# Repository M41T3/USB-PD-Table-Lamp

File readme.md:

# Table Lamp with USB PD Light Controller

## Contents

- Light controller PCB design
    - [Schematics](light_controller_pcb/light_controller_base/schematics.pdf)
    - [PCB design](light_controller_pcp/light_controller_base/pcb.pdf)
    - KiCad project
    - JLCPCB production files
- CAD designs (FreeCAD projects)
    - concrete lamp base mould
    - shade, light mount and knob

## 1. PCB design

The objective was to develop a highly configurable controller for various light sources that is powered via USB Power Delivery.

### Operation Modes

The operating mode can be configured using jumpers and potentiomenter wiring: 

1. Switch VBUS power and dimm light via PMW
2. Switch VBUS power and dimm light via constant current source
3. Low Side Switch and dimm light via PWM
4. Simple ON/OFF with disabled USB PD (5 V)
5. Switch VBUS power and fixed output current (set with jumpers)

### Noteable Features
- Configure output voltage and current 
    - Voltage: 5 V, 9 V, 12 V, 15 V, 20 V, 28 V
    - Current: 1.25 A - 3.25 A
    - Low power LED up to high power halogen lamps (35 W) supported
- Step-down converter to supply control units with all voltage levels
- Dimm light with PWM (555 Timer module)
- Constant current source to fine tune current 
- High power mosfet to switch light 
- 80 x 80 mm

#### USB PD ERP Sink controller ([HUSB238A](https://www.lcsc.com/datasheet/C24833806.pdf)):

- Fully Autonomous USB Type-C® and USB PD Sink Controller
- USB PD Specification Reversion 3.1 supported
- Integrated VBUS Switch Driver
- Error detection output (LED)

#### PWM Controller ([LMC555](https://www.lcsc.com/datasheet/C90760.pdf))

- CMOS variant of famous 555 general-purpose timer
- Duty cycle configurable by 100k potentiometer 

#### Constant Current Source ([PAM2861](https://www.lcsc.com/datasheet/C150496.pdf))

- 1 A LED driber with internal switch
- Adjustable output current (100k potentiometer)

#### Step-Down Converter ([TPS54302](https://www.ti.com/lit/ds/symlink/tps54302.pdf))

- Converts variable VUSB voltage to 5 V to supply 555 timer and constant current control

#### 100 kOhm Potentiometer with Rotary Switch ([WSFA202-A2-08-30F1](https://asset.conrad.com/media10/add/160267/c1/-/en/000441431DS01/tehnicni-podatki-441431-potenciometer-z-10-a-stikalomweltron-wsfa202-a2-08-30f1-10k-20-lin-10-kiloohmov-002045040444.pdf))

## 2. Concrete Lamp Base

The lamp's base was made of concrete. To do this, a mold was designed and printed using a 3D printer with PLA. The controller board is installed inside the lamp's base.

### Mould

The mold is designed so that it can be taken apart into separate pieces after curing.

The seams are sealed with hot glue.

The liquid concrete is poured into the mold up to the top edge:

### Box of Shame
To be honest, it took three attempts with different modifications to the base design before I was able to get the concrete piece out of the mold in one piece...

### Base installations

To position the light source in the right spot, a 3D-printed bracket is screwed onto the circuit board: 

PCB, potentiomenter, knob and magnets are installed to the base:

Bottom: 

## 3. Shade

The lamp base was designed so that the light shade can be attached using magnets. This means the shade can be easily swapped out. This shade was designed so that it can be 3D-printed in vase mode.

## 4. Light it up!

Operating Mode: Switch VBUS and dimm light via PWM with potentiometer

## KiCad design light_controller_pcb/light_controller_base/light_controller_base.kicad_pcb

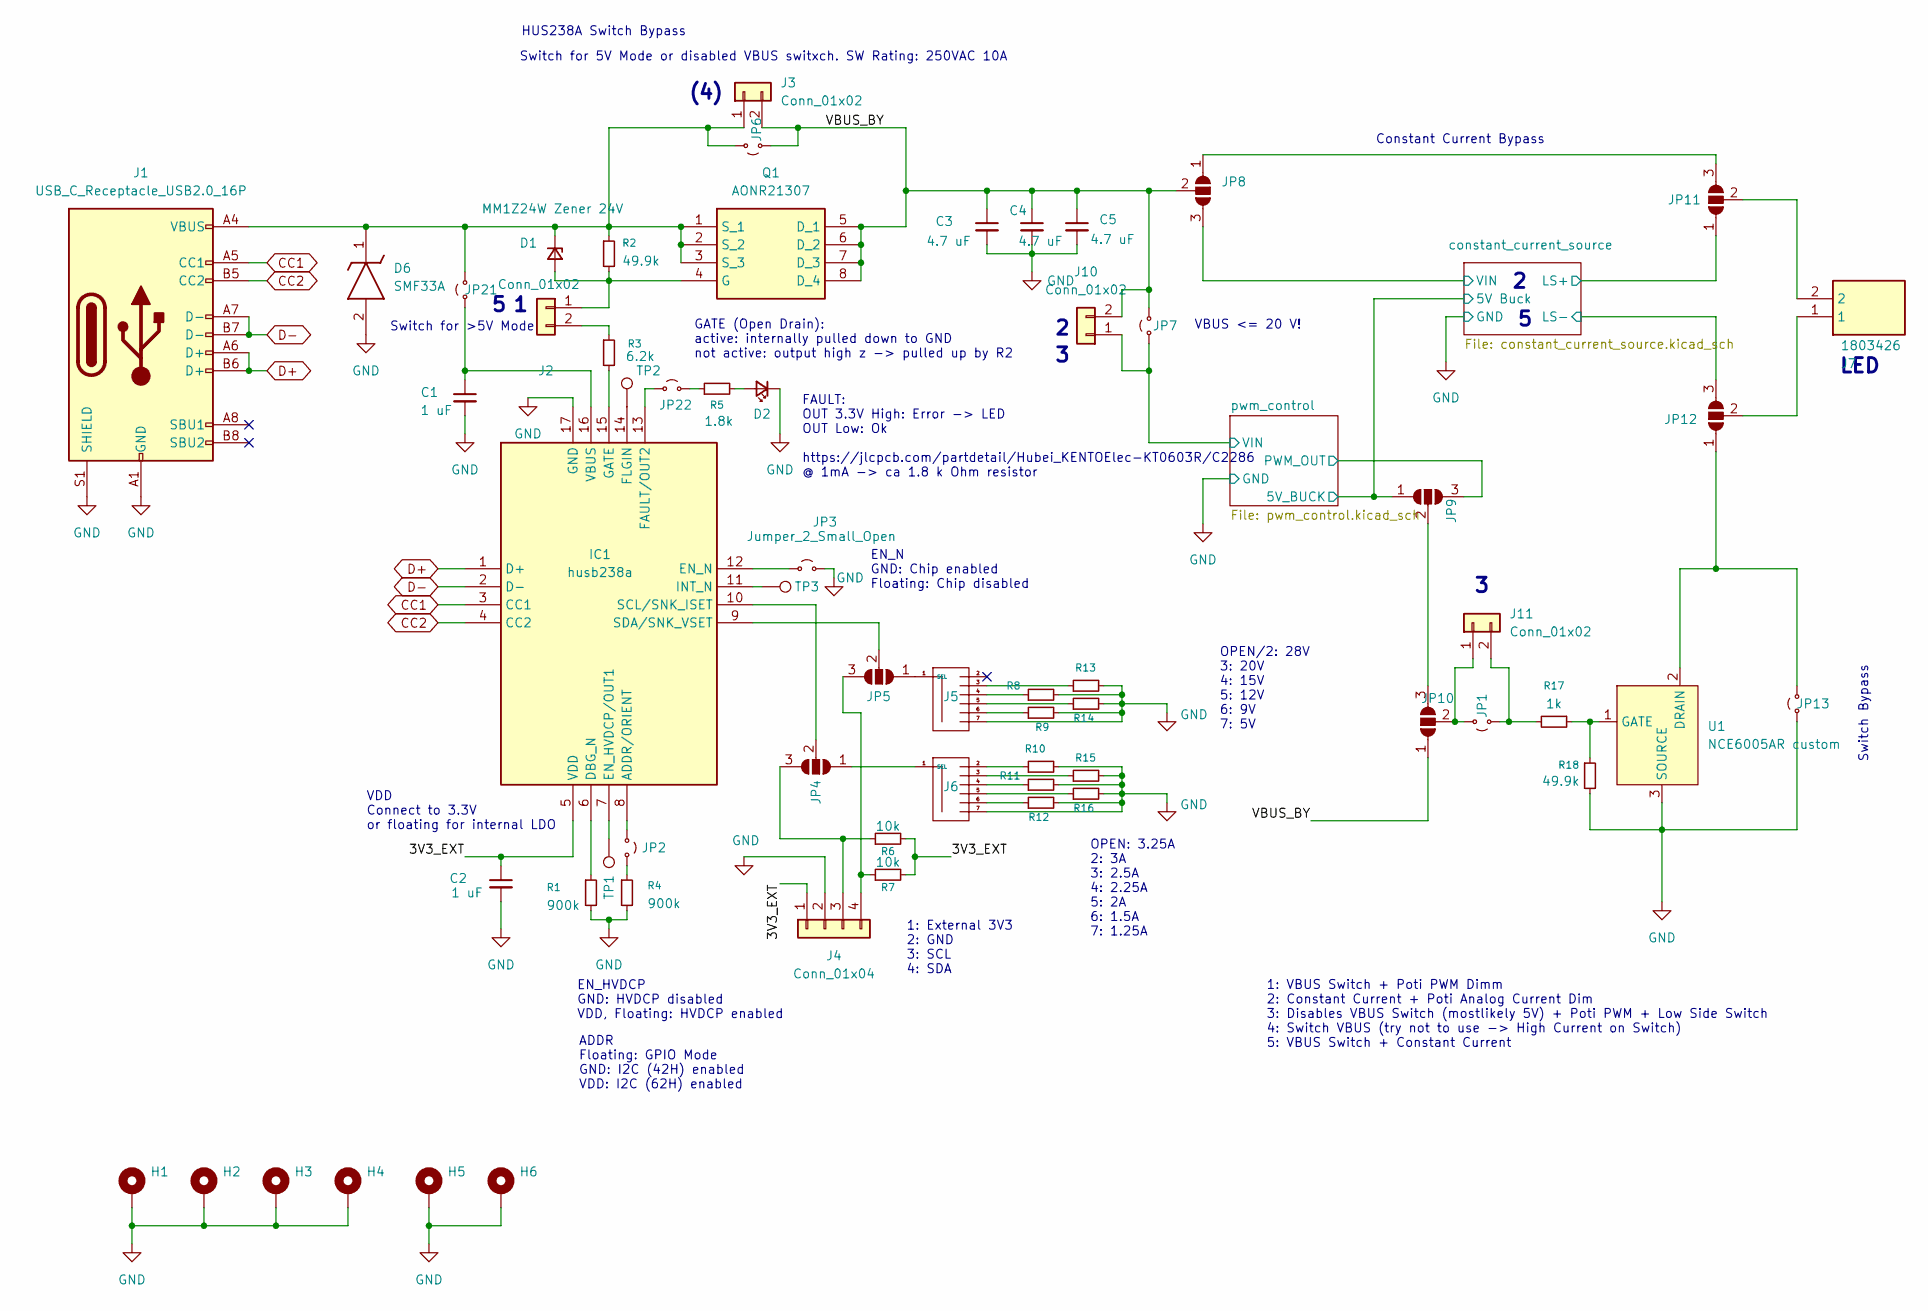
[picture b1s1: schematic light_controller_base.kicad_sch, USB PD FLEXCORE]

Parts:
C1, C2: 1 uF; C_0603_1608Metric; LCSC C15849
C3, C4, C5: 4.7 uF; C_1206_3216Metric; LCSC C29823
D1: MM1Z24W Zener 24V; Nexperia_CFP3_SOD-123W; LCSC C2856870
D2: LED_0603_1608Metric; LCSC C2286
D6: SMF33A; SODFL3618X110N; Manufacturer_Part_Number SMF33A; Mouser Part Number 637-SMF33A
H1, H2, H3, H4, H5, H6: MountingHole_Pad; MountingHole_3.2mm_M3_DIN965_Pad_TopBottom
IC1: husb238a; QFN50P300X300X80-17N-D; Manufacturer_Part_Number husb238a; LCSC C24833806
J1: USB_C_Receptacle_USB2.0_16P; USB_C_Receptacle_GCT_USB4105-xx-A_16P_TopMnt_Horizontal; LCSC C165948
J2, J3, J10, J11: Conn_01x02; JST_PH_B2B-PH-K_1x02_P2.00mm_Vertical
J4: Conn_01x04; JST_PH_B4B-PH-K_1x04_P2.00mm_Vertical
J5, J6: PinHeader_select_2x06_P2.54mm
J7: 1803426; Manufacturer_Part_Number 1803426; Mouser Part Number 651-1803426
JP1, JP3, JP7, JP21, JP22: Jumper_2_Small_Open; PinHeader_1x02_P2.54mm_Vertical
JP2: Jumper_2_Small_Open; SolderJumper-2_P1.3mm_Open_RoundedPad1.0x1.5mm
JP4, JP5: SolderJumper_3_Open; SolderJumper-3_P1.3mm_Bridged12_RoundedPad1.0x1.5mm
JP6, JP13: Jumper_2_Small_Open; PinHeader_doubled_2x02_P2.54mm
JP8, JP11, JP12: SolderJumper_3_Open; PinHeader_doubled_2x03_P2.54mm
JP9, JP10: SolderJumper_3_Open; PinHeader_1x03_P2.54mm_Vertical
Q1: AONR21307; DFN_3X3_EP; Manufacturer_Part_Number AONR21307; LCSC C3277813
R1, R4: 900k; R_0805_2012Metric; LCSC C52209984
R2, R18: 49.9k; R_0603_1608Metric; LCSC C23184
R3: 6.2k; R_0603_1608Metric; LCSC C4260
R5: 1.8k; R_0603_1608Metric; LCSC C4177
R6, R7: 10k; R_0603_1608Metric; LCSC C25804
R8: 11k; R_0603_1608Metric; LCSC C25950
R9: 3k; R_0603_1608Metric; LCSC C4211
R10: 21k; R_0603_1608Metric; LCSC C22956
R11: 8.45k; R_0603_1608Metric; LCSC C163417
R12: 2.26k; R_0603_1608Metric; LCSC C22904
R13: 19.1k; R_0603_1608Metric; LCSC C22897
R14, R16: 6.04k; R_0603_1608Metric; LCSC C25977
R15: 11.5k; R_0603_1608Metric; LCSC C25949
R17: 1k; R_0603_1608Metric; LCSC C21190
TP1, TP2, TP3: TestPoint; TestPoint_Keystone_5015_Micro_Mini
U1: NCE6005AR custom; SOT-223-3_TabPin2; LCSC C189606

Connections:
/3V3_EXT: C2.1, IC1.5 (VDD), J4.1, R6.2, R7.2
/VBUS_BY: C3.1, C4.1, C5.1, J3.2, J10.2, JP6.1 (A), JP7.2 (B), JP8.2 (C), JP10.1 (A), Q1.5 (D_1), Q1.6 (D_2), Q1.7 (D_3), Q1.8 (D_4)
/constant_current_source/LS+: JP11.1 (A); also elsewhere on the board
/constant_current_source/LS-: JP12.3 (B); also elsewhere on the board
/constant_current_source/VIN: JP8.3 (B); also elsewhere on the board
/pwm_control/5V: JP9.1 (A); also elsewhere on the board
/pwm_control/PWM_OUT: JP9.3 (B); also elsewhere on the board
/pwm_control/VIN: J10.1, JP7.1 (A); also elsewhere on the board
CC1: IC1.3 (CC1), J1.A5 (CC1)
CC2: IC1.4 (CC2), J1.B5 (CC2)
D+: IC1.1 (D+), J1.A6 (D+), J1.B6 (D+)
D-: IC1.2 (D-), J1.A7 (D-), J1.B7 (D-)
GND: C1.2, C2.2, C3.2, C4.2, C5.2, D2.1 (K), D6.2 (A), H1.1, H2.1, H3.1, H4.1, H5.1, H6.1, IC1.17 (GND), J1.A1 (GND), J1.A12 (GND), J1.B1 (GND), J1.B12 (GND), J1.S1 (SHIELD), J4.2, J5.7, J6.7, JP3.2 (B), JP13.1 (A), R1.2, R4.2, R8.2, R9.2, R10.2, R11.2, R12.2, R13.2, R14.2, R15.2, R16.2, R18.2, U1.3 (SOURCE); also elsewhere on the board
unnamed: D1.2 (A), J2.1, Q1.4 (G), R2.2
unnamed: D1.1 (K), D6.1 (K), J1.A4 (VBUS), J1.A9 (VBUS), J1.B4 (VBUS), J1.B9 (VBUS), J3.1, JP6.2 (B), JP21.2 (B), Q1.1 (S_1), Q1.2 (S_2), Q1.3 (S_3), R2.1
unnamed: D2.2 (A), R5.2
unnamed: IC1.8 (ADDR/ORIENT), JP2.1 (A)
unnamed: IC1.6 (DBG_N), R1.1
unnamed: IC1.7 (EN_HVDCP/OUT1), TP1.1
unnamed: IC1.12 (EN_N), JP3.1 (A)
unnamed: IC1.13 (FAULT/OUT2), JP22.1 (A)
unnamed: IC1.14 (FLGIN), TP2.1
unnamed: IC1.15 (GATE), R3.2
unnamed: IC1.11 (INT_N), TP3.1
unnamed: IC1.10 (SCL/SNK_ISET), JP4.2 (C)
unnamed: IC1.9 (SDA/SNK_VSET), JP5.2 (C)
unnamed: C1.1, IC1.16 (VBUS), JP21.1 (A)
unnamed: J2.2, R3.1
unnamed: J4.3, JP4.3 (B), R6.1
unnamed: J4.4, JP5.3 (B), R7.1
unnamed: J5.3, R13.1
unnamed: J5.4, R8.1
unnamed: J5.5, R14.1
unnamed: J5.6, R9.1
unnamed: J5.1 (SEL), JP5.1 (A)
unnamed: J6.2, R10.1
unnamed: J6.3, R15.1
unnamed: J6.4, R11.1
unnamed: J6.5, R16.1
unnamed: J6.6, R12.1
unnamed: J6.1 (SEL), JP4.1 (A)
unnamed: J11.1, JP1.2 (B), JP10.2 (C)
unnamed: J11.2, JP1.1 (A), R17.2
unnamed: JP2.2 (B), R4.1
unnamed: JP9.2 (C), JP10.3 (B)
unnamed: JP8.1 (A), JP11.3 (B)
unnamed: J7.2, JP11.2 (C)
unnamed: JP12.1 (A), JP13.2 (B), U1.2 (DRAIN)
unnamed: J7.1, JP12.2 (C)
unnamed: JP22.2 (B), R5.1
unnamed: R17.1, R18.1, U1.1 (GATE)

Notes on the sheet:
HUS238A Switch Bypass
Switch for 5V Mode or disabled VBUS switxch. SW Rating: 250VAC 10A
Switch for >5V Mode
FAULT: OUT 3.3V High: Error -> LED OUT Low: Ok https://jlcpcb.com/partdetail/Hubei_KENTOElec-KT0603R/C2286 @ 1mA -> ca 1.8 k Ohm resistor
Constant Current Bypass
1: VBUS Switch + Poti PWM Dimm 2: Constant Current + Poti Analog Current Dim 3: Disables VBUS Switch (mostlikely 5V) + Poti PWM + Low Side Switch 4: Switch VBUS (try not to use -> High Current on Switch) 5: VBUS Switch + Constant Current
OPEN: 3.25A 2: 3A 3: 2.5A 4: 2.25A 5: 2A 6: 1.5A 7: 1.25A
EN_HVDCP GND: HVDCP disabled VDD, Floating: HVDCP enabled
LED
GATE (Open Drain): active: internally pulled down to GND not active: output high z -> pulled up by R2
1: External 3V3 2: GND 3: SCL 4: SDA
OPEN/2: 28V 3: 20V 4: 15V 5: 12V 6: 9V 7: 5V
VBUS <= 20 V!
Switch Bypass
VDD Connect to 3.3V or floating for internal LDO
ADDR Floating: GPIO Mode GND: I2C (42H) enabled VDD: I2C (62H) enabled
(4)
EN_N GND: Chip enabled Floating: Chip disabled

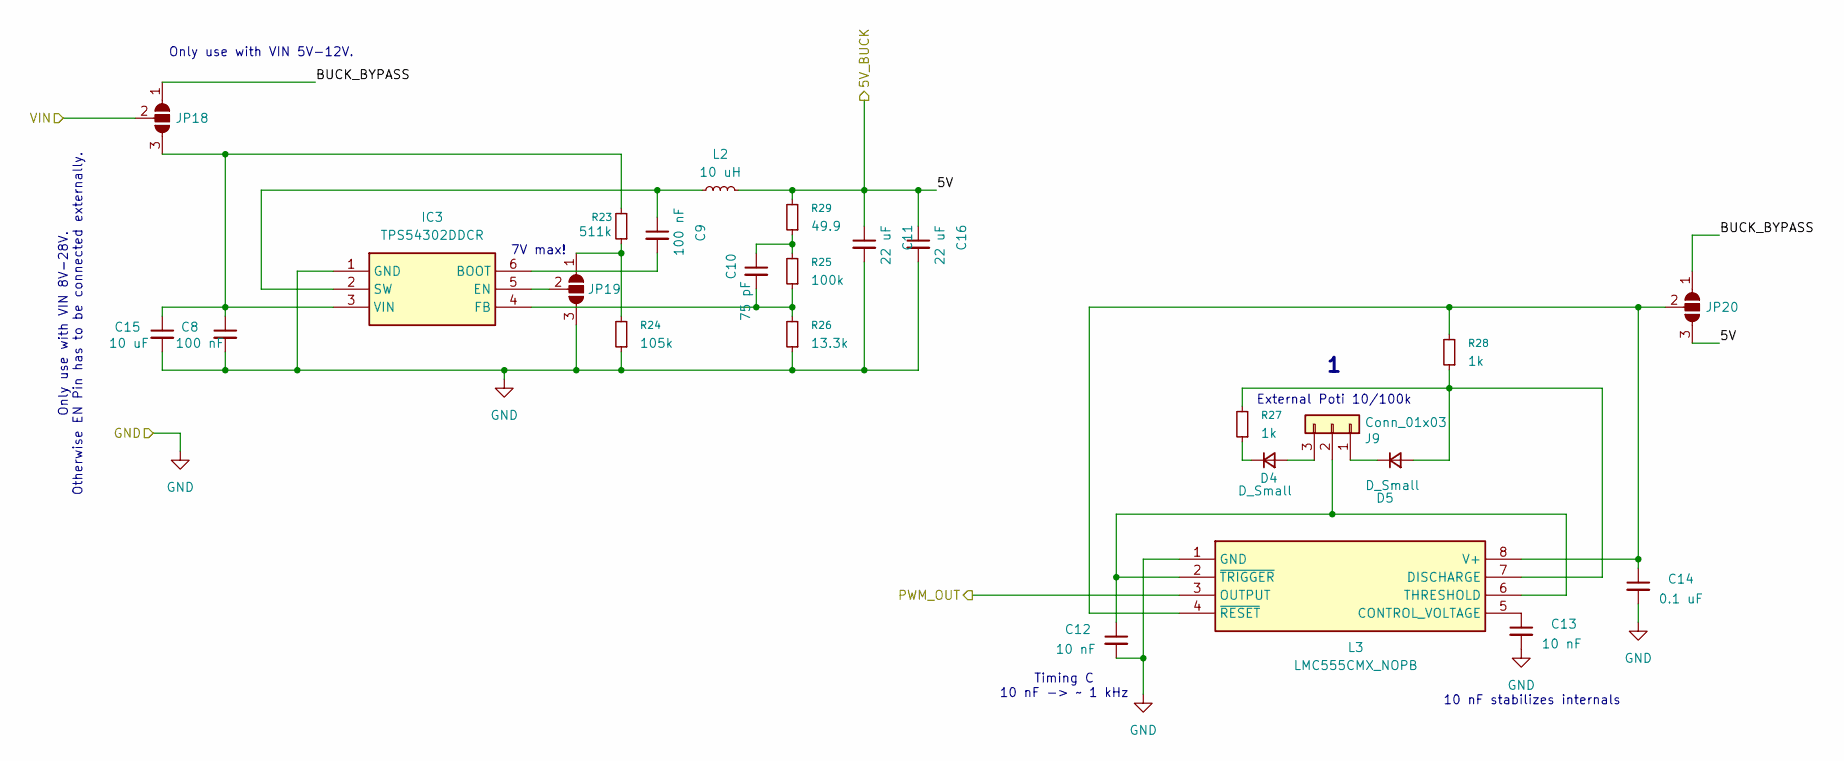
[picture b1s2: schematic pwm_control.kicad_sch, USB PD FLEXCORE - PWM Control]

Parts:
C8, C9: 100 nF; C_0603_1608Metric; LCSC C14663
C10: 75 pF; C_0603_1608Metric; LCSC C1681
C11, C16: 22 uF; C_1206_3216Metric; LCSC C12891
C12, C13: 10 nF; C_0603_1608Metric; LCSC C57112
C14: 0.1 uF; C_0603_1608Metric; LCSC C14663
C15: 10 uF; C_1206_3216Metric; LCSC C13585
D4, D5: D_Small; D_SOD-123; LCSC C81598
IC3: TPS54302DDCR; SOT95P280X110-6N; Manufacturer_Part_Number TPS54302DDCR; Mouser Part Number 595-TPS54302DDCR
J9: Conn_01x03; JST_PH_B3B-PH-K_1x03_P2.00mm_Vertical
JP18, JP19, JP20: SolderJumper_3_Open; PinHeader_1x03_P2.54mm_Vertical
L2: 10 uH; L_5.2_5.4_smd; LCSC C351099
L3: LMC555CMX_NOPB; SOIC127P600X175-8N; Manufacturer_Part_Number LMC555CMX/NOPB; Mouser Part Number 926-LMC555CMX/NOPB
R23: 511k; R_0603_1608Metric; LCSC C23194
R24: 105k; R_0603_1608Metric; LCSC C16840
R25: 100k; R_0603_1608Metric; LCSC C25803
R26: 13.3k; R_0603_1608Metric; LCSC C25952
R27, R28: 1k; R_0603_1608Metric; LCSC C21190
R29: 49.9; R_0603_1608Metric; LCSC C23185

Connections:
/pwm_control/5V: C11.1, C16.1, JP20.3 (B), L2.2, R29.2; also elsewhere on the board
/pwm_control/BUCK_BYPASS: JP18.1 (A), JP20.1 (A)
/pwm_control/PWM_OUT: L3.3 (OUTPUT); also elsewhere on the board
/pwm_control/VIN: JP18.2 (C); also elsewhere on the board
GND: C8.2, C11.2, C12.2, C13.2, C14.2, C15.2, C16.2, IC3.1 (GND), JP19.3 (B), L3.1 (GND), R24.1, R26.1; also elsewhere on the board
unnamed: C10.1, R25.2, R29.1
unnamed: D4.2 (A), J9.3
unnamed: D4.1 (K), R27.1
unnamed: D5.2 (A), L3.7 (DISCHARGE), R27.2, R28.1
unnamed: D5.1 (K), J9.1
unnamed: C9.2, IC3.6 (BOOT)
unnamed: IC3.5 (EN), JP19.2 (C)
unnamed: C10.2, IC3.4 (FB), R25.1, R26.2
unnamed: C9.1, IC3.2 (SW), L2.1
unnamed: C8.1, C15.1, IC3.3 (VIN), JP18.3 (B), R23.2
unnamed: C12.1, J9.2, L3.2 (~TRIGGER), L3.6 (THRESHOLD)
unnamed: JP19.1 (A), R23.1, R24.2
unnamed: C14.1, JP20.2 (C), L3.4 (~RESET), L3.8 (V+), R28.2
unnamed: C13.1, L3.5 (CONTROL_VOLTAGE)

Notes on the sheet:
Only use with VIN 5V-12V.
7V max!
Timing C 10 nF -> ~ 1 kHz
External Poti 10/100k
10 nF stabilizes internals
Only use with VIN 8V-28V. Otherwise EN Pin has to be connected externally.

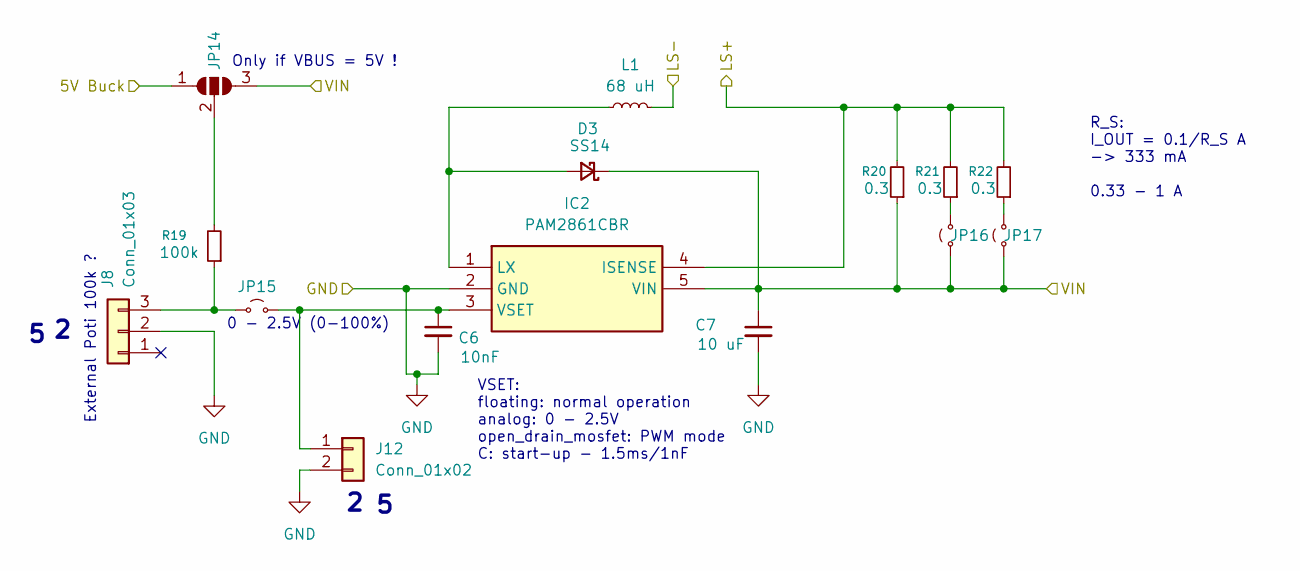
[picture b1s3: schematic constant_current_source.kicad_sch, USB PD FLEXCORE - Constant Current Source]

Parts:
C6: 10nF; C_0603_1608Metric; LCSC C57112
C7: 10 uF; C_1206_3216Metric; LCSC C13585
D3: SS14; D_SMA; LCSC C2480
IC2: PAM2861CBR; SOT89-5; Manufacturer_Part_Number PAM2861CBR; Mouser Part Number 621-PAM2861CBR
J8: Conn_01x03; JST_PH_B3B-PH-K_1x03_P2.00mm_Vertical
J12: Conn_01x02; JST_PH_B2B-PH-K_1x02_P2.00mm_Vertical
JP14: SolderJumper_3_Open; PinHeader_1x03_P2.54mm_Vertical
JP15, JP16, JP17: Jumper_2_Small_Open; PinHeader_1x02_P2.54mm_Vertical
L1: 68 uH; L_6.6_7.1_smd; LCSC C2983094
R19: 100k; R_0603_1608Metric; LCSC C25803
R20, R21, R22: 0.3; R_1206_3216Metric; LCSC C59882

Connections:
/constant_current_source/LS+: IC2.4 (ISENSE), R20.2, R21.2, R22.2; also elsewhere on the board
/constant_current_source/LS-: L1.2; also elsewhere on the board
/constant_current_source/VIN: C7.1, D3.1 (K), IC2.5 (VIN), JP14.3 (B), JP16.1 (A), JP17.1 (A), R20.1; also elsewhere on the board
/pwm_control/5V: JP14.1 (A); also elsewhere on the board
GND: C6.2, C7.2, IC2.2 (GND), J8.2, J12.2; also elsewhere on the board
unnamed: D3.2 (A), IC2.1 (LX), L1.1
unnamed: C6.1, IC2.3 (VSET), J12.1, JP15.2 (B)
unnamed: J8.3, JP15.1 (A), R19.1
unnamed: JP14.2 (C), R19.2
unnamed: JP16.2 (B), R21.1
unnamed: JP17.2 (B), R22.1

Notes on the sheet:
VSET: floating: normal operation analog: 0 - 2.5V open_drain_mosfet: PWM mode C: start-up - 1.5ms/1nF
External Poti 100k ?
0 - 2.5V (0-100%)
R_S: I_OUT = 0.1/R_S A -> 333 mA 0.33 - 1 A
Only if VBUS = 5V !

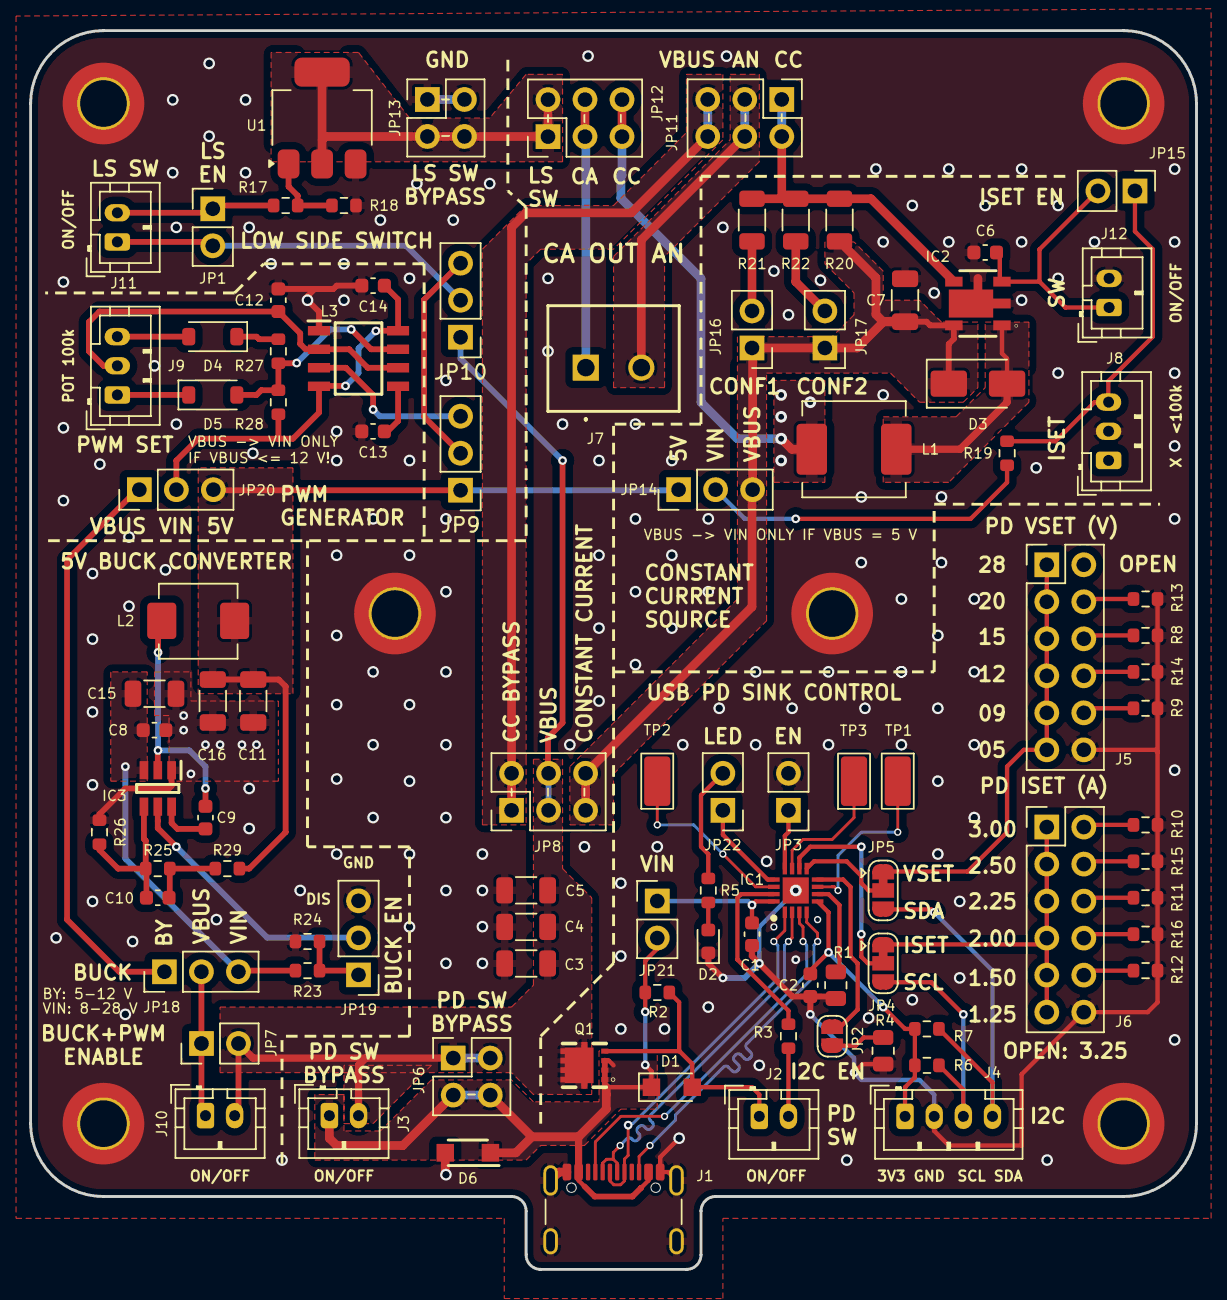
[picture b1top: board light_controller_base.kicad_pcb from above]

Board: 2 copper layers, 80.0 x 85.0 mm, 102 parts (0 on the bottom side), 72 nets.

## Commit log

2026-03-21 fix relative paths

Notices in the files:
light_controller_pcb/light_controller_base/light_controller_base.kicad_pcb:
CC BYPASS
